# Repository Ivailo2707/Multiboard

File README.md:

# Multiboard
Multifunctional PCB with microcontroller and FPGA for embedded systems development

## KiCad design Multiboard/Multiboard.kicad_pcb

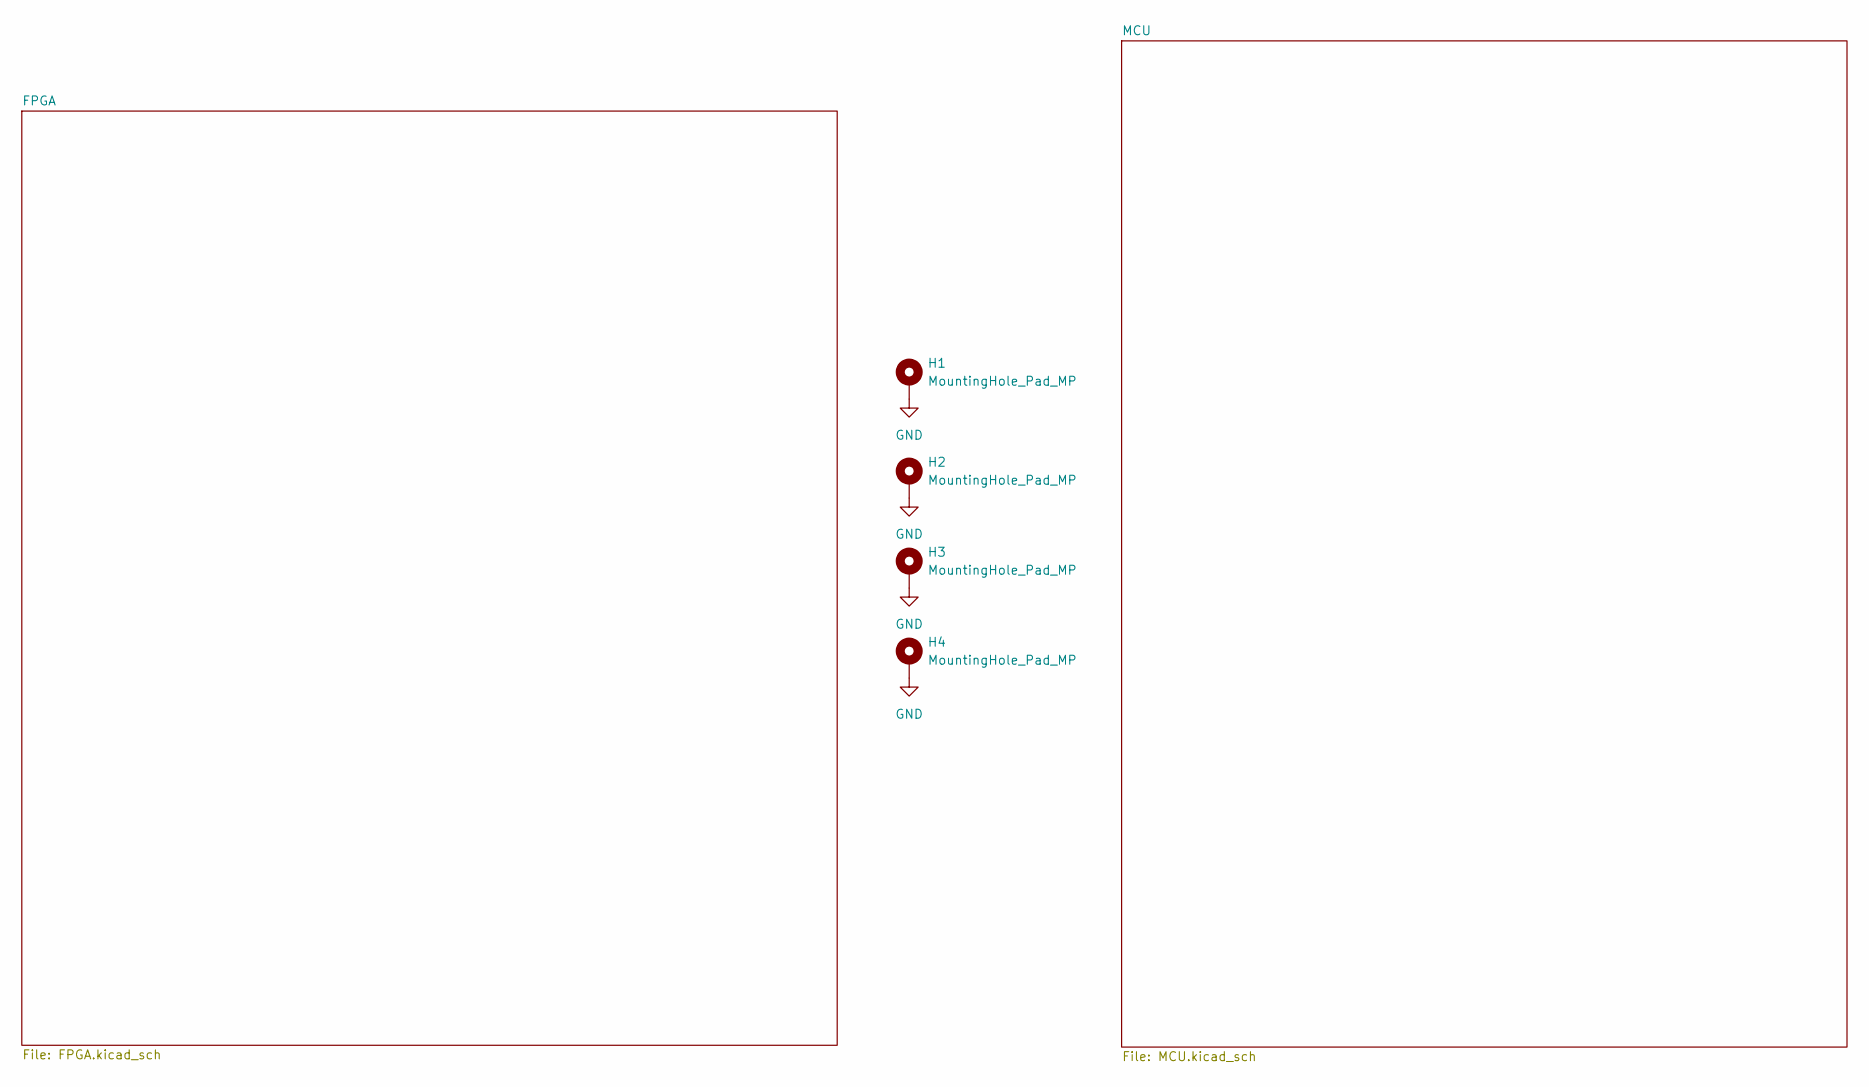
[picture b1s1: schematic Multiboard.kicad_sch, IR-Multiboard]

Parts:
H1, H2, H3, H4: MountingHole_Pad_MP; MountingHole_3.2mm_M3_DIN965_Pad_TopBottom

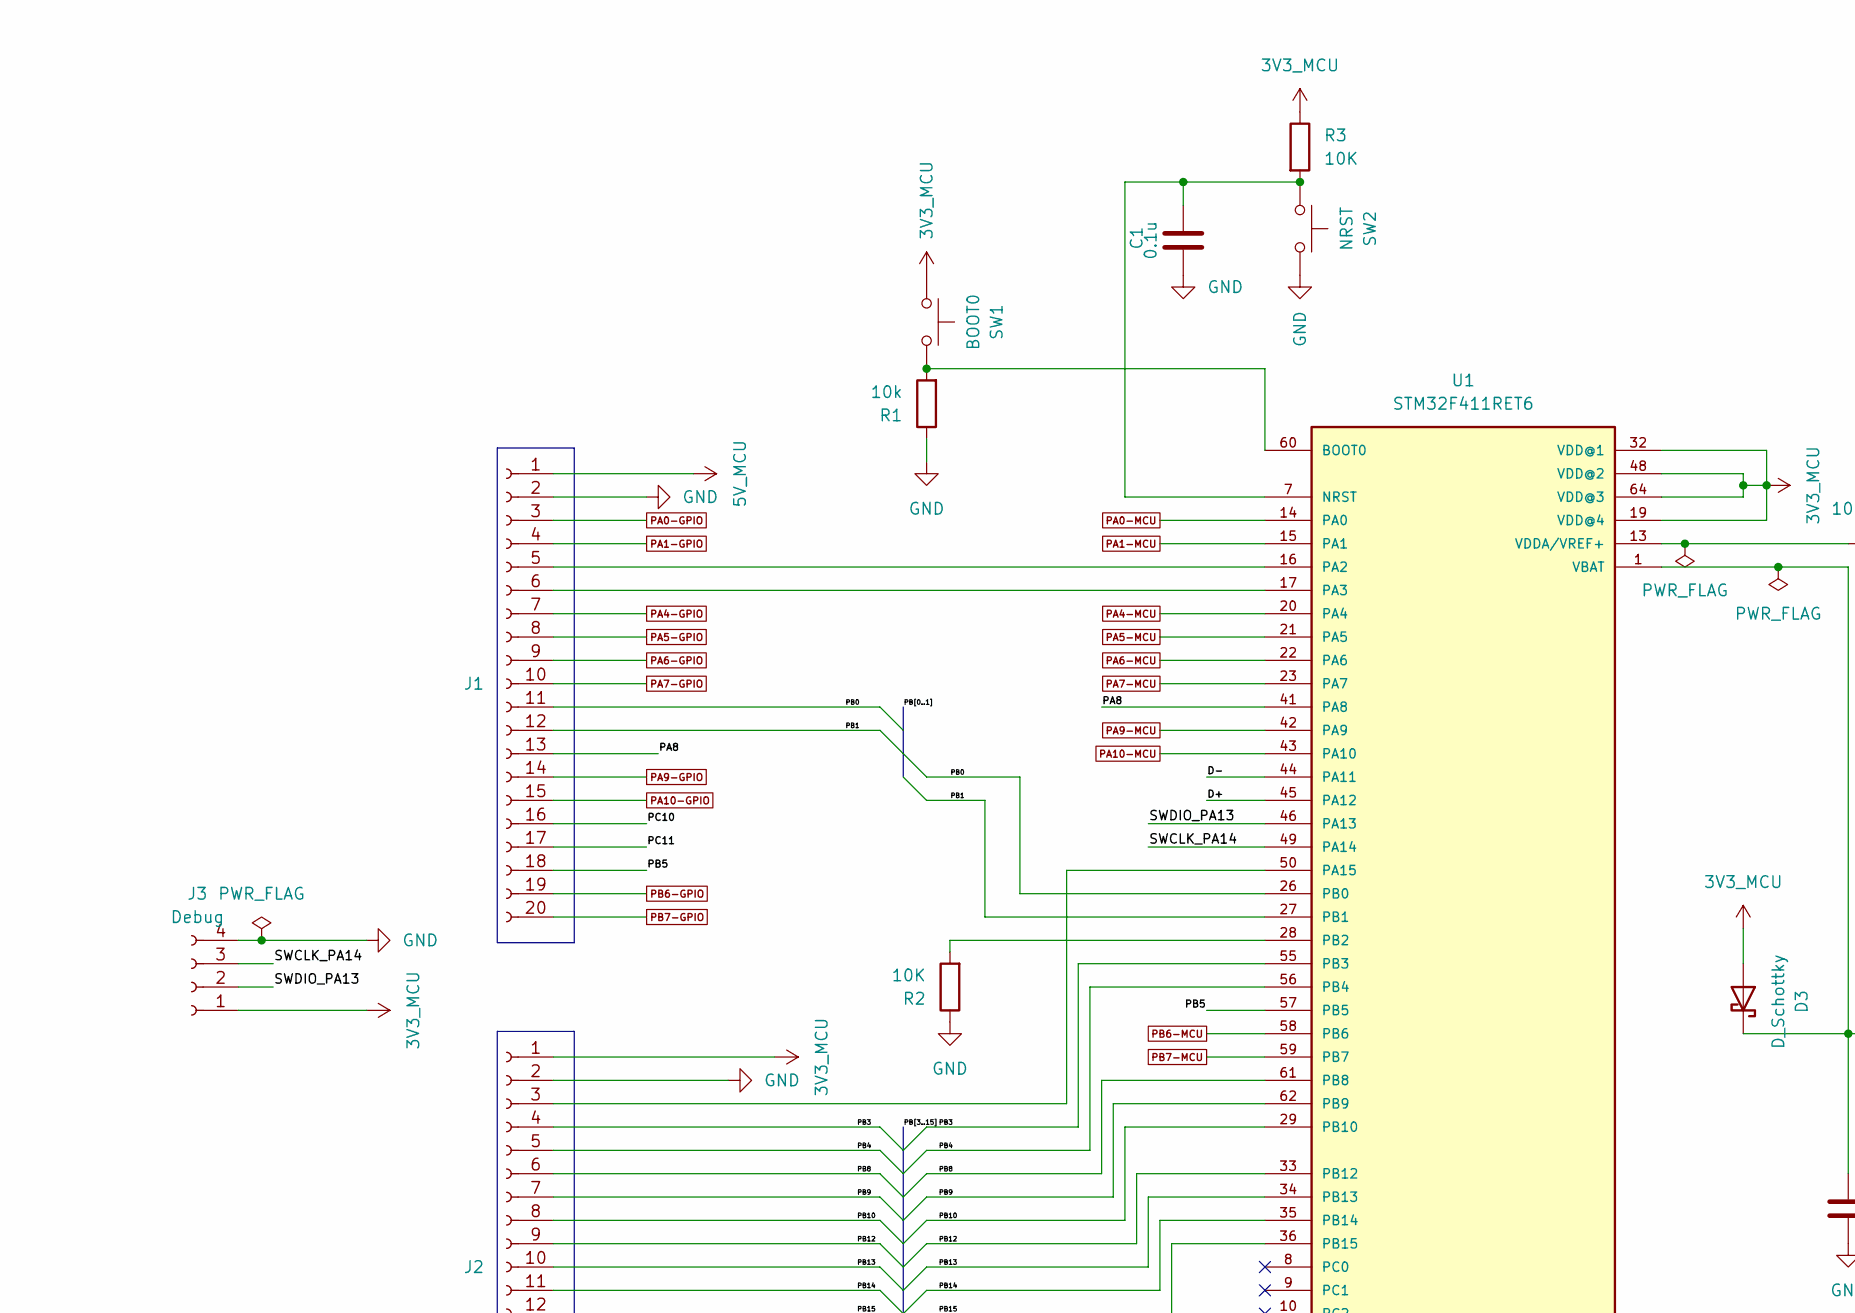
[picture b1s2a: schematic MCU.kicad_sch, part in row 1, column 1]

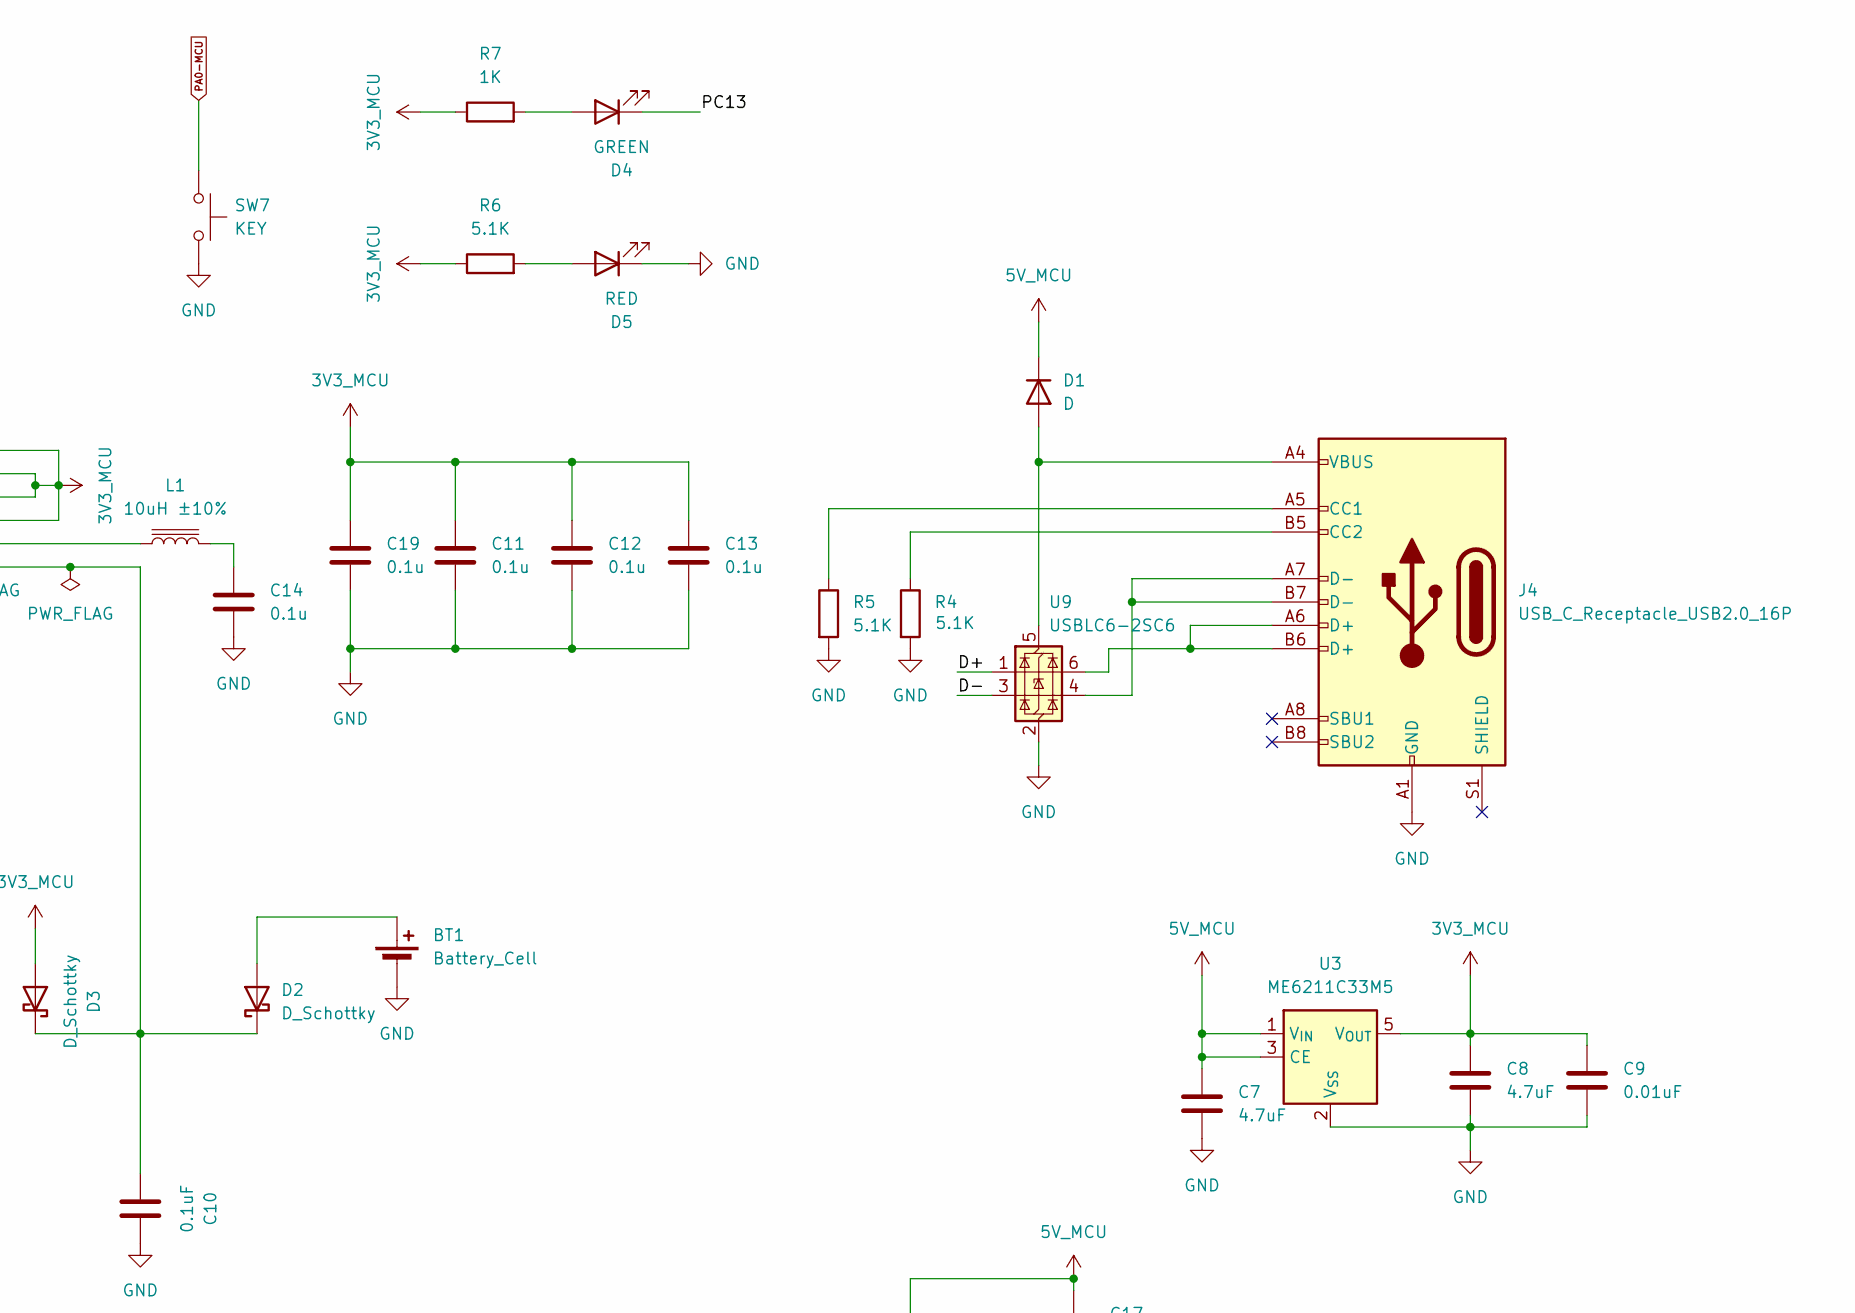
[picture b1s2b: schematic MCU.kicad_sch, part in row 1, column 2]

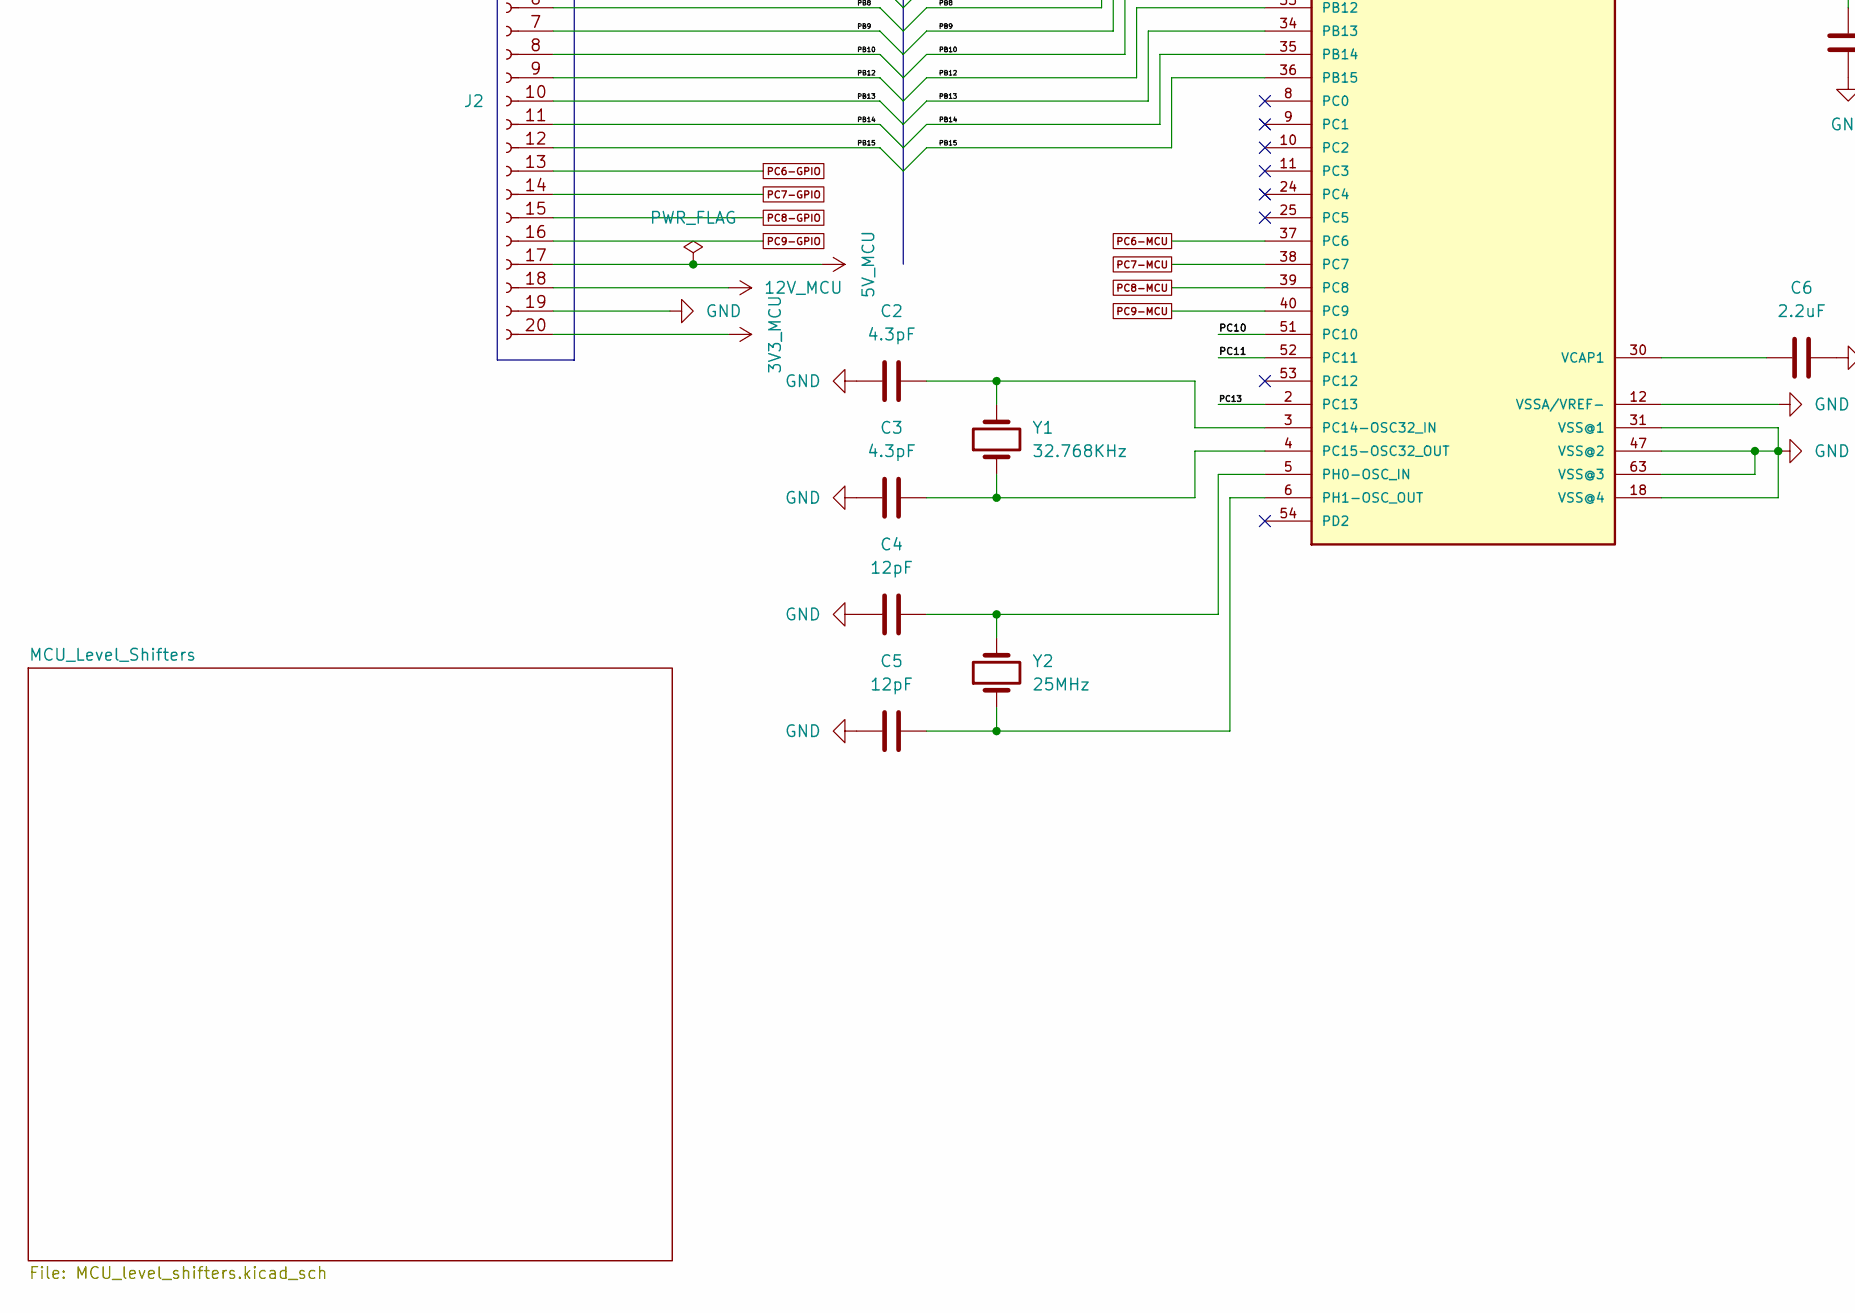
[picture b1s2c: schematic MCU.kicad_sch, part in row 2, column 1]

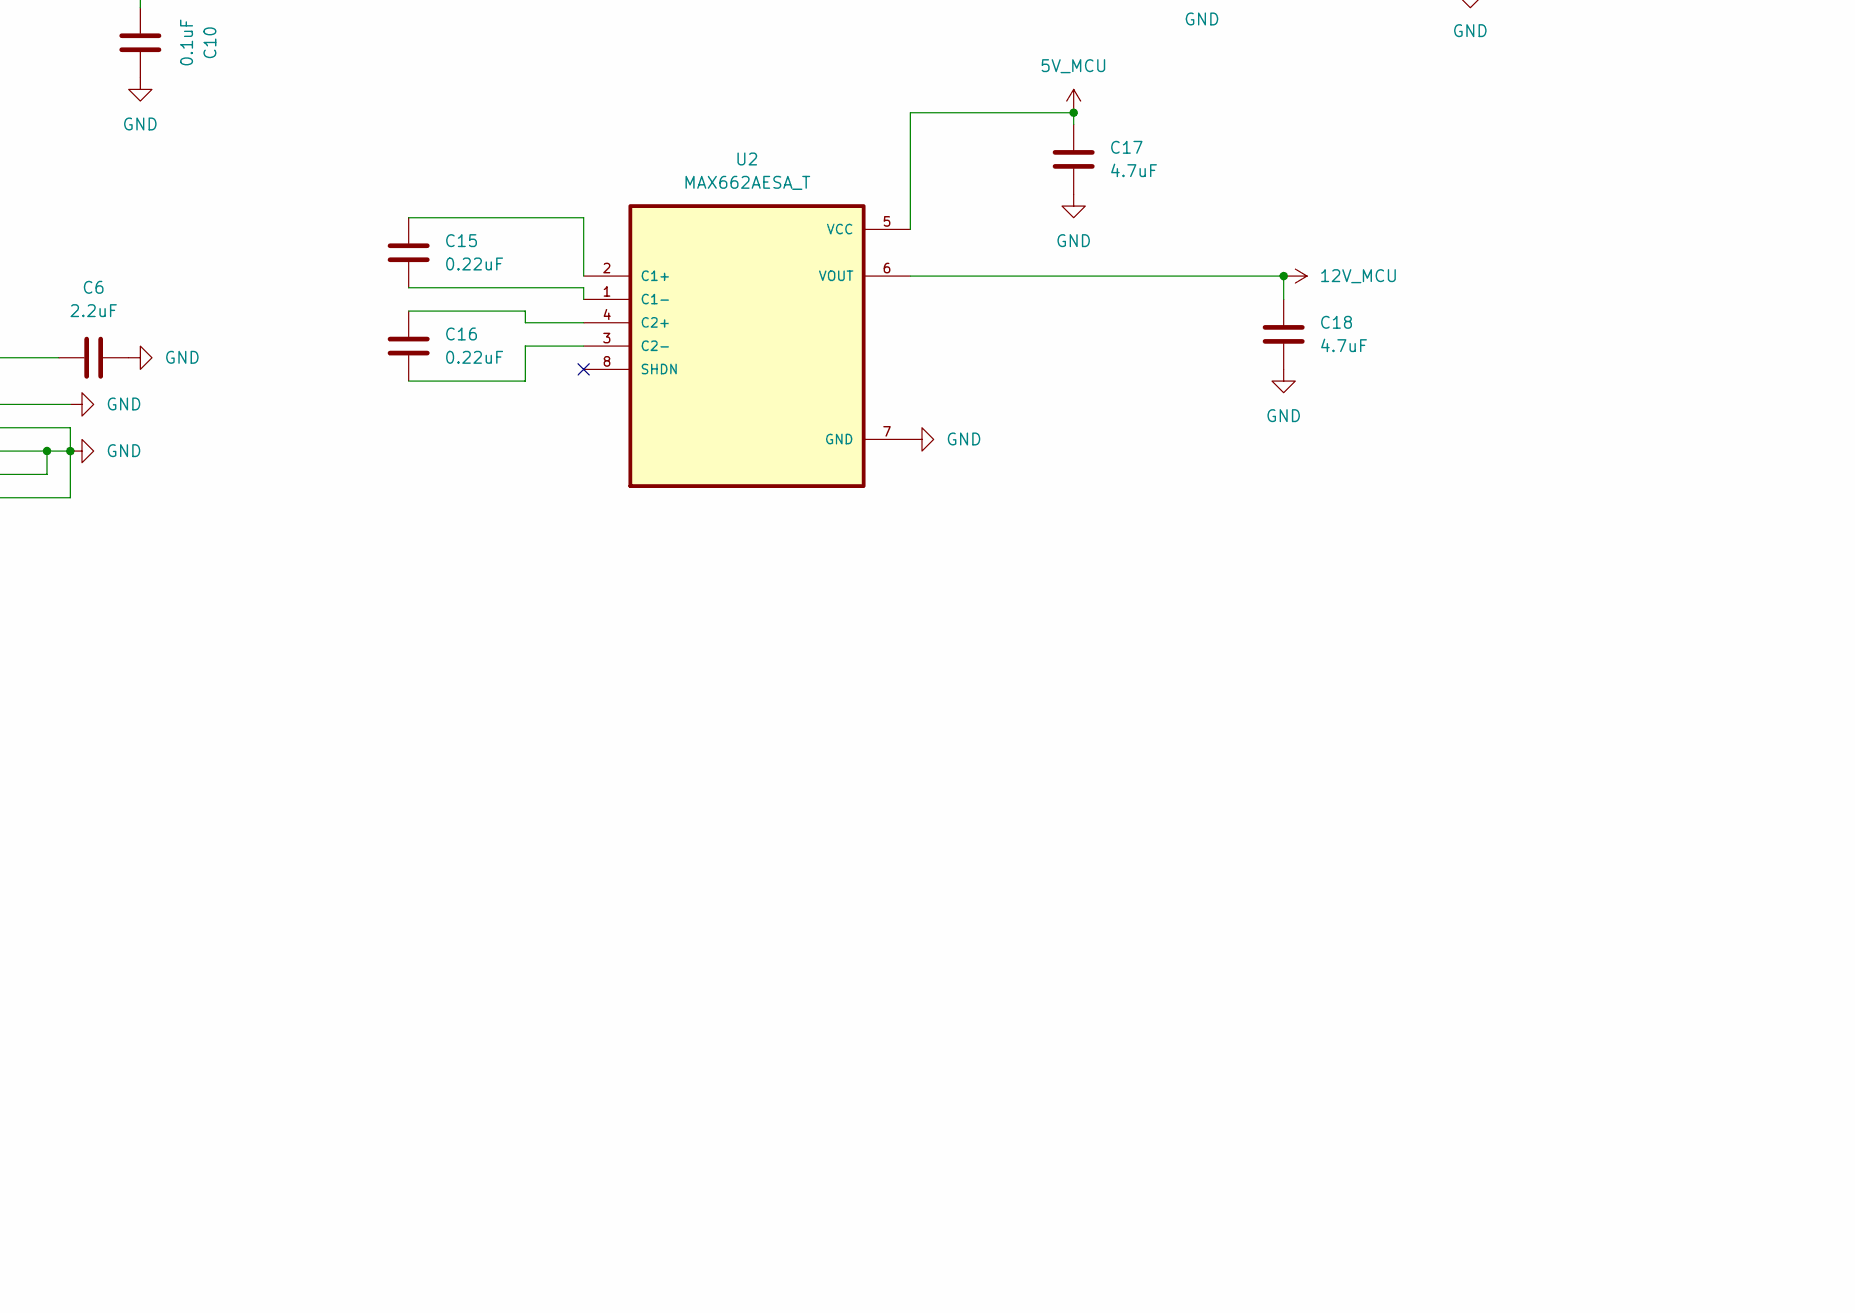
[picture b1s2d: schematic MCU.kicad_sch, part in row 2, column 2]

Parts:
BT1: Battery_Cell; Battery_Panasonic_CR2032-VS1N_Vertical_CircularHoles
C1, C11, C12, C13, C14, C19: 0.1u; C_0603_1608Metric_Pad1.08x0.95mm_HandSolder; LCSC Part Number C14663
C2, C3: 4.3pF; C_0603_1608Metric_Pad1.08x0.95mm_HandSolder; LCSC Part Number C519375
C4, C5: 12pF; C_0603_1608Metric_Pad1.08x0.95mm_HandSolder; LCSC Part Number C38523
C6: 2.2uF; C_0603_1608Metric_Pad1.08x0.95mm_HandSolder; LCSC Part Number C913904
C7, C8, C17: 4.7uF; C_0603_1608Metric_Pad1.08x0.95mm_HandSolder; LCSC Part Number C19666
C9: 0.01uF; C_0603_1608Metric_Pad1.08x0.95mm_HandSolder; LCSC Part Number C100042
C10: 0.1uF; C_0603_1608Metric_Pad1.08x0.95mm_HandSolder; LCSC Part Number C14663
C15, C16: 0.22uF; C_0603_1608Metric_Pad1.08x0.95mm_HandSolder; LCSC Part Number C64705
C18: 4.7uF; C_0603_1608Metric_Pad1.08x0.95mm_HandSolder; LCSC Part Number C161217
D1: D; D_0603_1608Metric_Pad1.05x0.95mm_HandSolder
D2, D3: D_Schottky; D_SOD-323F; LCSC Part Number C2903903
D4: GREEN; LED_0603_1608Metric_Pad1.05x0.95mm_HandSolder; LCSC Part Number C2994781
D5: RED; LED_0603_1608Metric_Pad1.05x0.95mm_HandSolder; LCSC Part Number C2846640
J1, J2: Conn_01x20_Socket; PinHeader_1x20_P2.54mm_Vertical
J3: Debug; Hirose_DF13-04P-1.25DSA_1x04_P1.25mm_Vertical
J4: USB_C_Receptacle_USB2.0_16P; USB_C_Receptacle_G-Switch_GT-USB-7010ASV; LCSC Part Number C2988369
L1: 10uH ±10%; L_0603_1608Metric_Pad1.05x0.95mm_HandSolder; LCSC Part Number C6808014
R1: 10k; R_0603_1608Metric_Pad0.98x0.95mm_HandSolder; LCSC Part Number C98220
R2, R3: 10K; R_0603_1608Metric_Pad0.98x0.95mm_HandSolder; LCSC Part Number C98220
R4, R5, R6: 5.1K; R_0603_1608Metric_Pad0.98x0.95mm_HandSolder; LCSC Part Number C2907044
R7: 1K; R_0603_1608Metric_Pad0.98x0.95mm_HandSolder; LCSC Part Number C22548
SW1: BOOT0; SW_PUSH_6mm; LCSC Part Number C7528752
SW2: NRST; SW_PUSH_6mm; LCSC Part Number C7528752
SW7: KEY; SW_PUSH_6mm; LCSC Part Number C7528752
U1: STM32F411RET6; QFP50P1200X1200X160-64N; LCSC Part Number C94355
U2: MAX662AESA_T; SOIC127P600X175-8N; LCSC Part Number C2976348
U3: ME6211C33M5; SOT-23-5_HandSoldering; LCSC Part Number C2984946
U9: USBLC6-2SC6; SOT-23-6; LCSC Part Number C7519
Y1: 32.768KHz; Crystal_SMD_3215-2Pin_3.2x1.5mm; LCSC Part Number C95361
Y2: 25MHz; Crystal_SMD_3225-4Pin_3.2x2.5mm; LCSC Part Number C255920

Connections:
3V3_MCU: C8.1, C9.1, C11.1, C12.1, C13.1, C19.1, D3.2 (A), J2.1, J2.20, J3.1, R3.1, R6.1, R7.1, SW1.1, U1.19 (VDD@4), U1.32 (VDD@1), U1.48 (VDD@2), U1.64 (VDD@3), U3.5 (V_{OUT}); also elsewhere on the board
5V_MCU: C7.1, C17.1, D1.1 (K), J1.1, J2.17, U2.5 (VCC), U3.1 (V_{IN}), U3.3 (CE); also elsewhere on the board
12V_MCU: C18.1, J2.18, U2.6 (VOUT)
/MCU/D+: U1.45 (PA12), U9.1 (I/O1)
/MCU/D-: U1.44 (PA11), U9.3 (I/O2)
/MCU/PA8: J1.13, U1.41 (PA8)
/MCU/PB0: J1.11, U1.26 (PB0)
/MCU/PB1: J1.12, U1.27 (PB1)
/MCU/PB3: J2.4, U1.55 (PB3)
/MCU/PB4: J2.5, U1.56 (PB4)
/MCU/PB5: J1.18, U1.57 (PB5)
/MCU/PB8: J2.6, U1.61 (PB8)
/MCU/PB9: J2.7, U1.62 (PB9)
/MCU/PB10: J2.8, U1.29 (PB10)
/MCU/PB12: J2.9, U1.33 (PB12)
/MCU/PB13: J2.10, U1.34 (PB13)
/MCU/PB14: J2.11, U1.35 (PB14)
/MCU/PB15: J2.12, U1.36 (PB15)
/MCU/PC10: J1.16, U1.51 (PC10)
/MCU/PC11: J1.17, U1.52 (PC11)
/MCU/PC13: D4.1 (K), U1.2 (PC13)
/MCU/SWCLK_PA14: J3.3, U1.49 (PA14)
/MCU/SWDIO_PA13: J3.2, U1.46 (PA13)
GND: BT1.2 (-), C1.2, C2.1, C3.1, C4.1, C5.1, C6.2, C7.2, C8.2, C9.2, C10.2, C11.2, C12.2, C13.2, C14.1, C17.2, C18.2, C19.2, D5.1 (K), J1.2, J2.2, J2.19, J3.4, J4.A1 (GND), J4.A12 (GND), J4.B1 (GND), J4.B12 (GND), R1.1, R2.1, R4.2, R5.2, SW2.2, SW7.2, U1.12 (VSSA/VREF-), U1.18 (VSS@4), U1.31 (VSS@1), U1.47 (VSS@2), U1.63 (VSS@3), U2.7 (GND), U3.2 (V_{SS}), U9.2 (GND); also elsewhere on the board
unnamed: C14.2, L1.2
unnamed: D1.2 (A), J4.A4 (VBUS), J4.A9 (VBUS), J4.B4 (VBUS), J4.B9 (VBUS), U9.5 (VBUS)
unnamed: C10.1, D2.1 (K), D3.1 (K), U1.1 (VBAT)
unnamed: D4.2 (A), R7.2
unnamed: D5.2 (A), R6.2
unnamed: J4.A5 (CC1), R5.1
unnamed: J4.B5 (CC2), R4.1
unnamed: J4.A6 (D+), J4.B6 (D+), U9.6 (I/O1)
unnamed: J4.A7 (D-), J4.B7 (D-), U9.4 (I/O2)
unnamed: R1.2, SW1.2, U1.60 (BOOT0)
unnamed: C1.1, R3.2, SW2.1, U1.7 (NRST)
unnamed: R2.2, U1.28 (PB2)
unnamed: C2.2, U1.3 (PC14-OSC32_IN), Y1.2
unnamed: C3.2, U1.4 (PC15-OSC32_OUT), Y1.1
unnamed: C4.2, U1.5 (PH0-OSC_IN), Y2.3
unnamed: C5.2, U1.6 (PH1-OSC_OUT), Y2.1
unnamed: C6.1, U1.30 (VCAP1)
unnamed: L1.1, U1.13 (VDDA/VREF+)
unnamed: C15.1, U2.2 (C1+)
unnamed: C15.2, U2.1 (C1-)
unnamed: C16.1, U2.4 (C2+)
unnamed: C16.2, U2.3 (C2-)
PA0-GPIO: J1.3; also elsewhere on the board
PA0-MCU: SW7.1, U1.14 (PA0); also elsewhere on the board
PA1-GPIO: J1.4; also elsewhere on the board
PA1-MCU: U1.15 (PA1); also elsewhere on the board
PA4-GPIO: J1.7; also elsewhere on the board
PA4-MCU: U1.20 (PA4); also elsewhere on the board
PA5-GPIO: J1.8; also elsewhere on the board
PA5-MCU: U1.21 (PA5); also elsewhere on the board
PA6-GPIO: J1.9; also elsewhere on the board
PA6-MCU: U1.22 (PA6); also elsewhere on the board
PA7-GPIO: J1.10; also elsewhere on the board
PA7-MCU: U1.23 (PA7); also elsewhere on the board
PA9-GPIO: J1.14; also elsewhere on the board
PA9-MCU: U1.42 (PA9); also elsewhere on the board
PA10-GPIO: J1.15; also elsewhere on the board
PA10-MCU: U1.43 (PA10); also elsewhere on the board
PB6-GPIO: J1.19; also elsewhere on the board
PB6-MCU: U1.58 (PB6); also elsewhere on the board
PB7-GPIO: J1.20; also elsewhere on the board
PB7-MCU: U1.59 (PB7); also elsewhere on the board
PC6-GPIO: J2.13; also elsewhere on the board
PC6-MCU: U1.37 (PC6); also elsewhere on the board
PC7-GPIO: J2.14; also elsewhere on the board
PC7-MCU: U1.38 (PC7); also elsewhere on the board
PC8-GPIO: J2.15; also elsewhere on the board
PC8-MCU: U1.39 (PC8); also elsewhere on the board
PC9-GPIO: J2.16; also elsewhere on the board
PC9-MCU: U1.40 (PC9); also elsewhere on the board
